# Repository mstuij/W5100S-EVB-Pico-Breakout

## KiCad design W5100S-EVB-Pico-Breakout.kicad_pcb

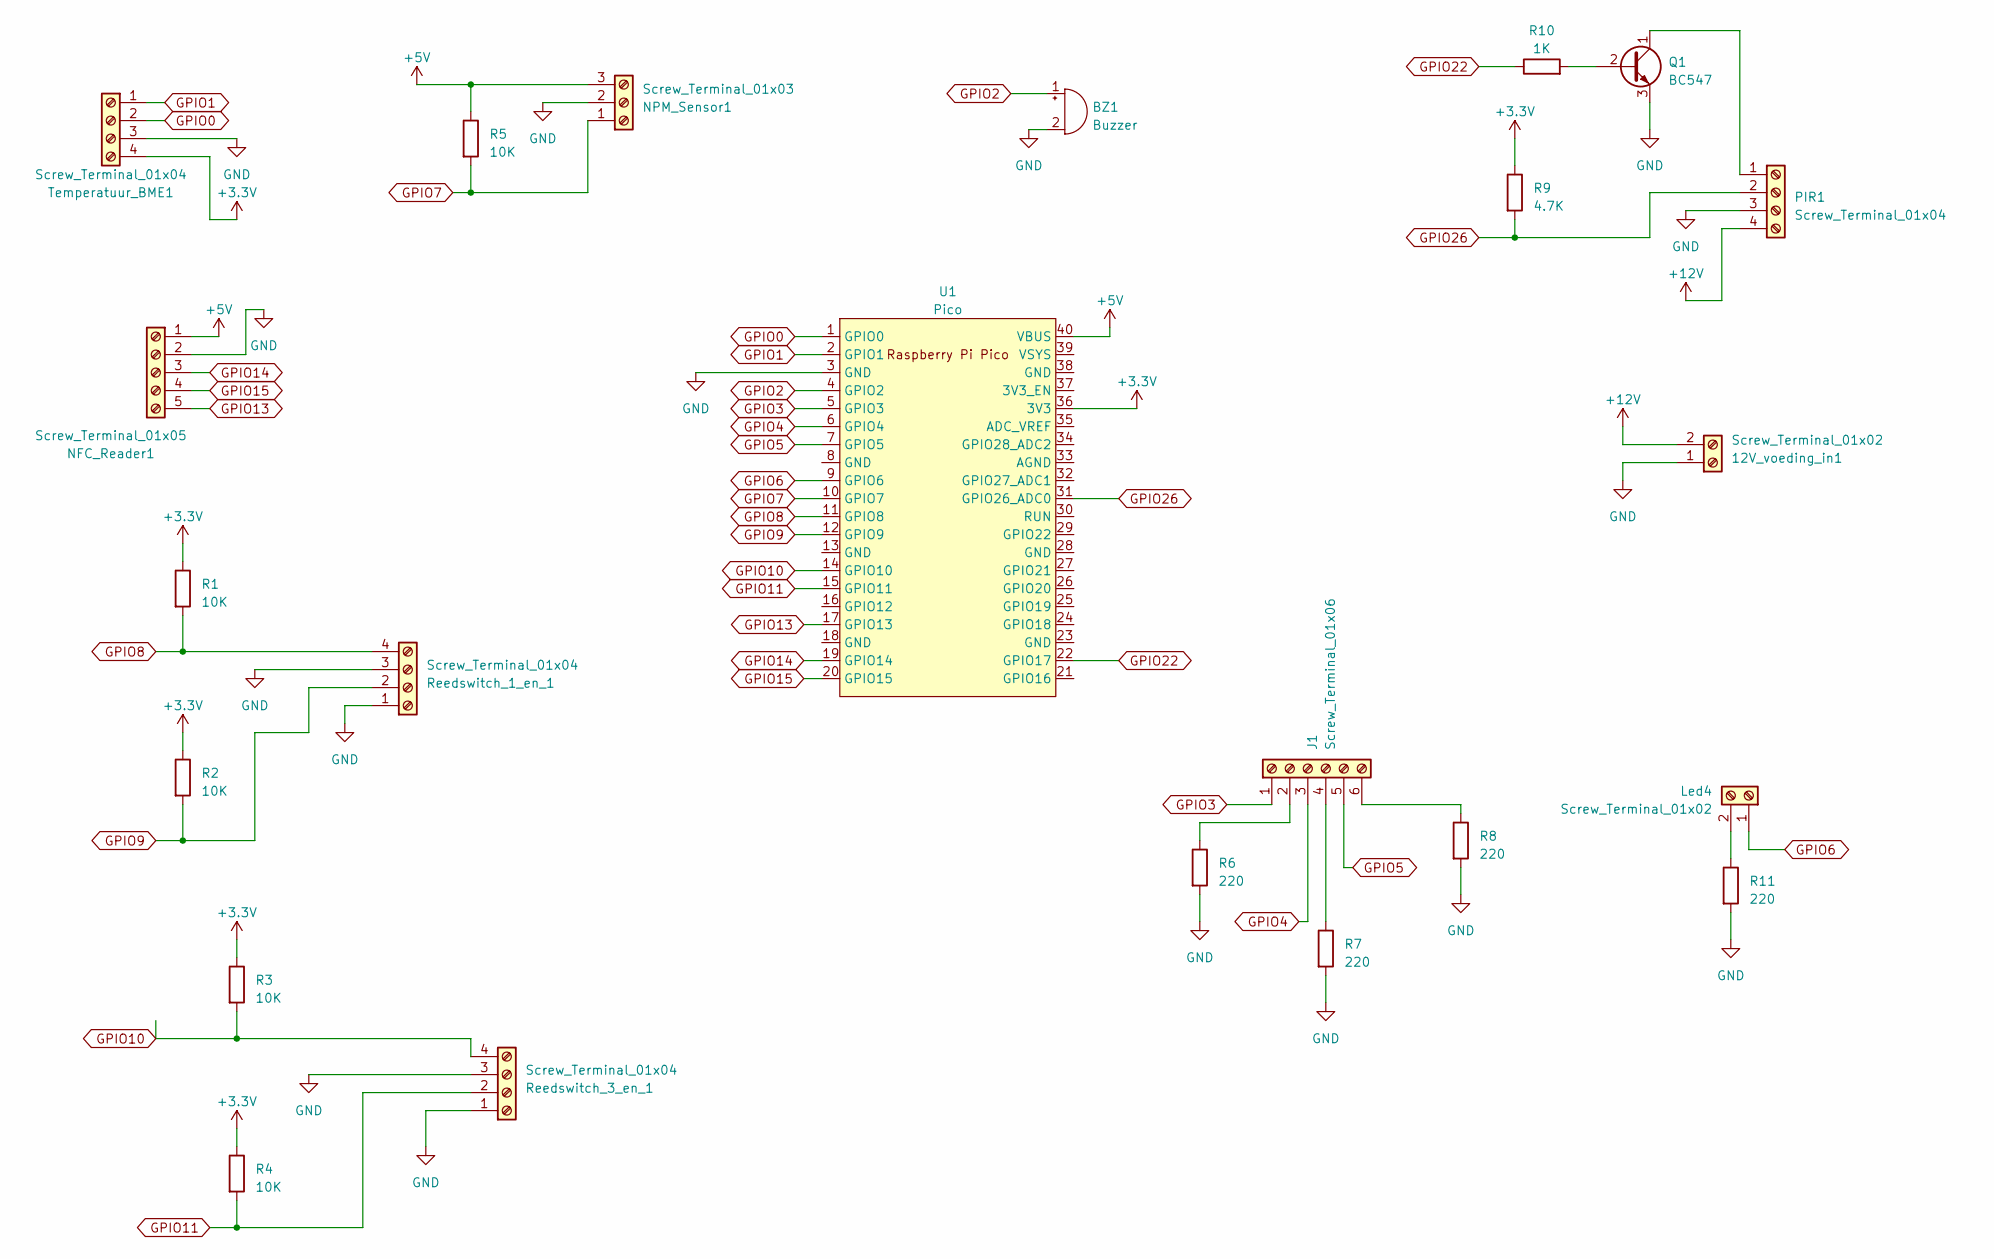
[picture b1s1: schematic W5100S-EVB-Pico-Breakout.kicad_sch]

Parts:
12V_voeding_in1: Screw_Terminal_01x02; TerminalBlock_MetzConnect_Type094_RT03502HBLU_1x02_P5.00mm_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
BZ1: Buzzer; Buzzer_12x9.5RM6.6_custom
J1: Screw_Terminal_01x06; TerminalBlock_MetzConnect_Type094_RT03506HBLU_1x06_P5.00mm_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
Led4: Screw_Terminal_01x02; TerminalBlock_MetzConnect_Type094_RT03502HBLU_1x02_P5.00mm_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
NFC_Reader1: Screw_Terminal_01x05; TerminalBlock_MetzConnect_Type094_RT03505HBLU_1x05_P5.00mm_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
NPM_Sensor1: Screw_Terminal_01x03; TerminalBlock_MetzConnect_Type094_RT03503HBLU_1x03_P5.00mm_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
PIR1: Screw_Terminal_01x04; TerminalBlock_MetzConnect_Type094_RT03504HBLU_1x04_P5.00mm_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
Q1: BC547; TO-92_Inline_Wide
R1, R2, R3, R4, R5: 10K; R_Axial_DIN0207_L6.3mm_D2.5mm_P15.24mm_Horizontal
R6, R7, R8, R11: 220; R_Axial_DIN0207_L6.3mm_D2.5mm_P15.24mm_Horizontal
R9: 4.7K; R_Axial_DIN0207_L6.3mm_D2.5mm_P15.24mm_Horizontal
R10: 1K; R_Axial_DIN0207_L6.3mm_D2.5mm_P15.24mm_Horizontal
Reedswitch_1_en_1, Reedswitch_3_en_1: Screw_Terminal_01x04; TerminalBlock_MetzConnect_Type094_RT03504HBLU_1x04_P5.00mm_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
Temperatuur_BME1: Screw_Terminal_01x04; TerminalBlock_MetzConnect_Type094_RT03504HBLU_1x04_P5.00mm_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
U1: Pico; W5100S-EVB-Pico

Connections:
+3.3V: R1.1, R2.1, R3.1, R4.1, R9.1, Temperatuur_BME1.4, U1.36 (3V3)
+5V: NFC_Reader1.1, NPM_Sensor1.3, R5.1, U1.40 (VBUS)
+12V: 12V_voeding_in1.2, PIR1.4
GND: 12V_voeding_in1.1, BZ1.2 (+), NFC_Reader1.2, NPM_Sensor1.2, PIR1.3, Q1.3 (E), R6.2, R7.2, R8.2, R11.2, Reedswitch_1_en_1.1, Reedswitch_1_en_1.3, Reedswitch_3_en_1.1, Reedswitch_3_en_1.3, Temperatuur_BME1.3, U1.3 (GND)
GPIO0: Temperatuur_BME1.2, U1.1 (GPIO0)
GPIO1: Temperatuur_BME1.1, U1.2 (GPIO1)
GPIO2: BZ1.1 (-), U1.4 (GPIO2)
GPIO3: J1.1, U1.5 (GPIO3)
GPIO4: J1.3, U1.6 (GPIO4)
GPIO5: J1.5, U1.7 (GPIO5)
GPIO6: Led4.1, U1.9 (GPIO6)
GPIO7: NPM_Sensor1.1, R5.2, U1.10 (GPIO7)
GPIO8: R1.2, Reedswitch_1_en_1.4, U1.11 (GPIO8)
GPIO9: R2.2, Reedswitch_1_en_1.2, U1.12 (GPIO9)
GPIO10: R3.2, Reedswitch_3_en_1.4, U1.14 (GPIO10)
GPIO11: R4.2, Reedswitch_3_en_1.2, U1.15 (GPIO11)
GPIO13: NFC_Reader1.5, U1.17 (GPIO13)
GPIO14: NFC_Reader1.3, U1.19 (GPIO14)
GPIO15: NFC_Reader1.4, U1.20 (GPIO15)
GPIO22: R10.1, U1.22 (GPIO17)
GPIO26: PIR1.2, R9.2, U1.31 (GPIO26_ADC0)
unnamed: J1.2, R6.1
unnamed: J1.4, R7.1
unnamed: J1.6, R8.1
unnamed: Led4.2, R11.1
unnamed: PIR1.1, Q1.1 (C)
unnamed: Q1.2 (B), R10.2

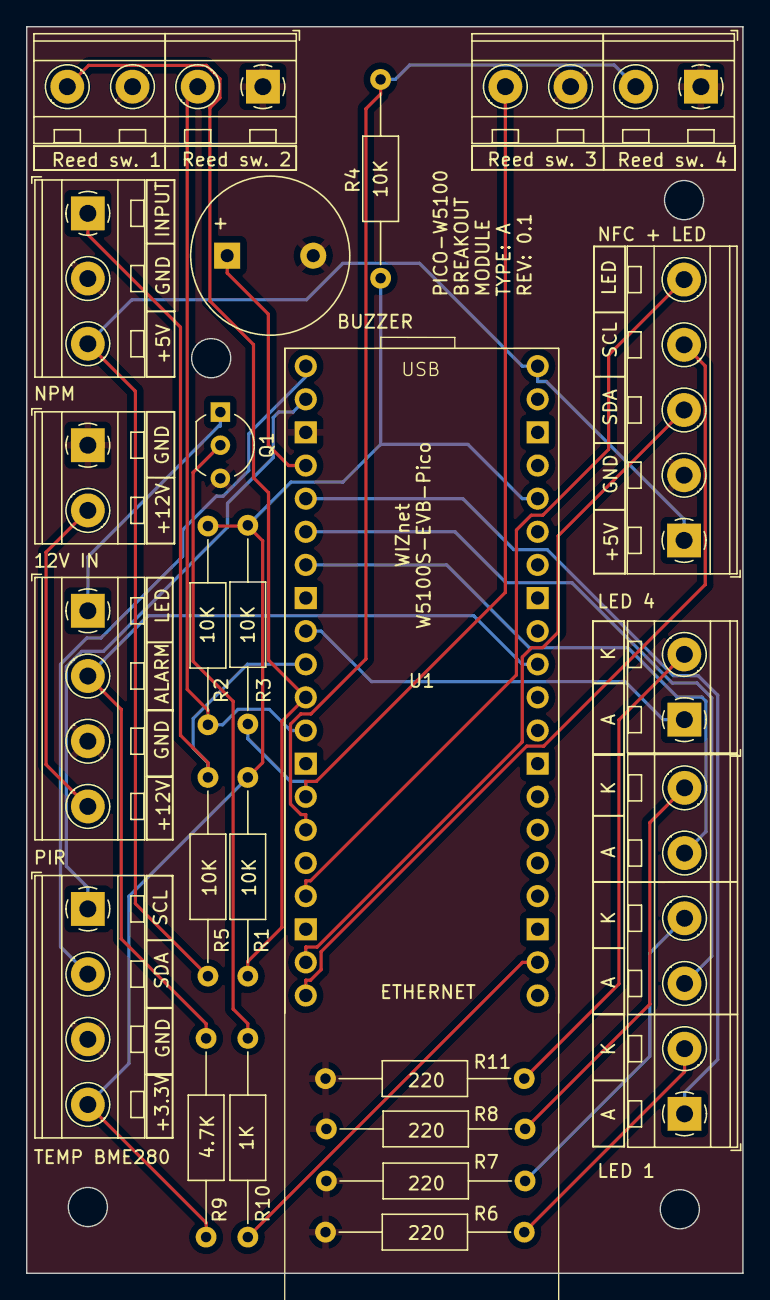
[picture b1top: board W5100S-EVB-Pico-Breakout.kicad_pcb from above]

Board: 2 copper layers, 54.9 x 95.6 mm, 23 parts (0 on the bottom side), 27 nets.
